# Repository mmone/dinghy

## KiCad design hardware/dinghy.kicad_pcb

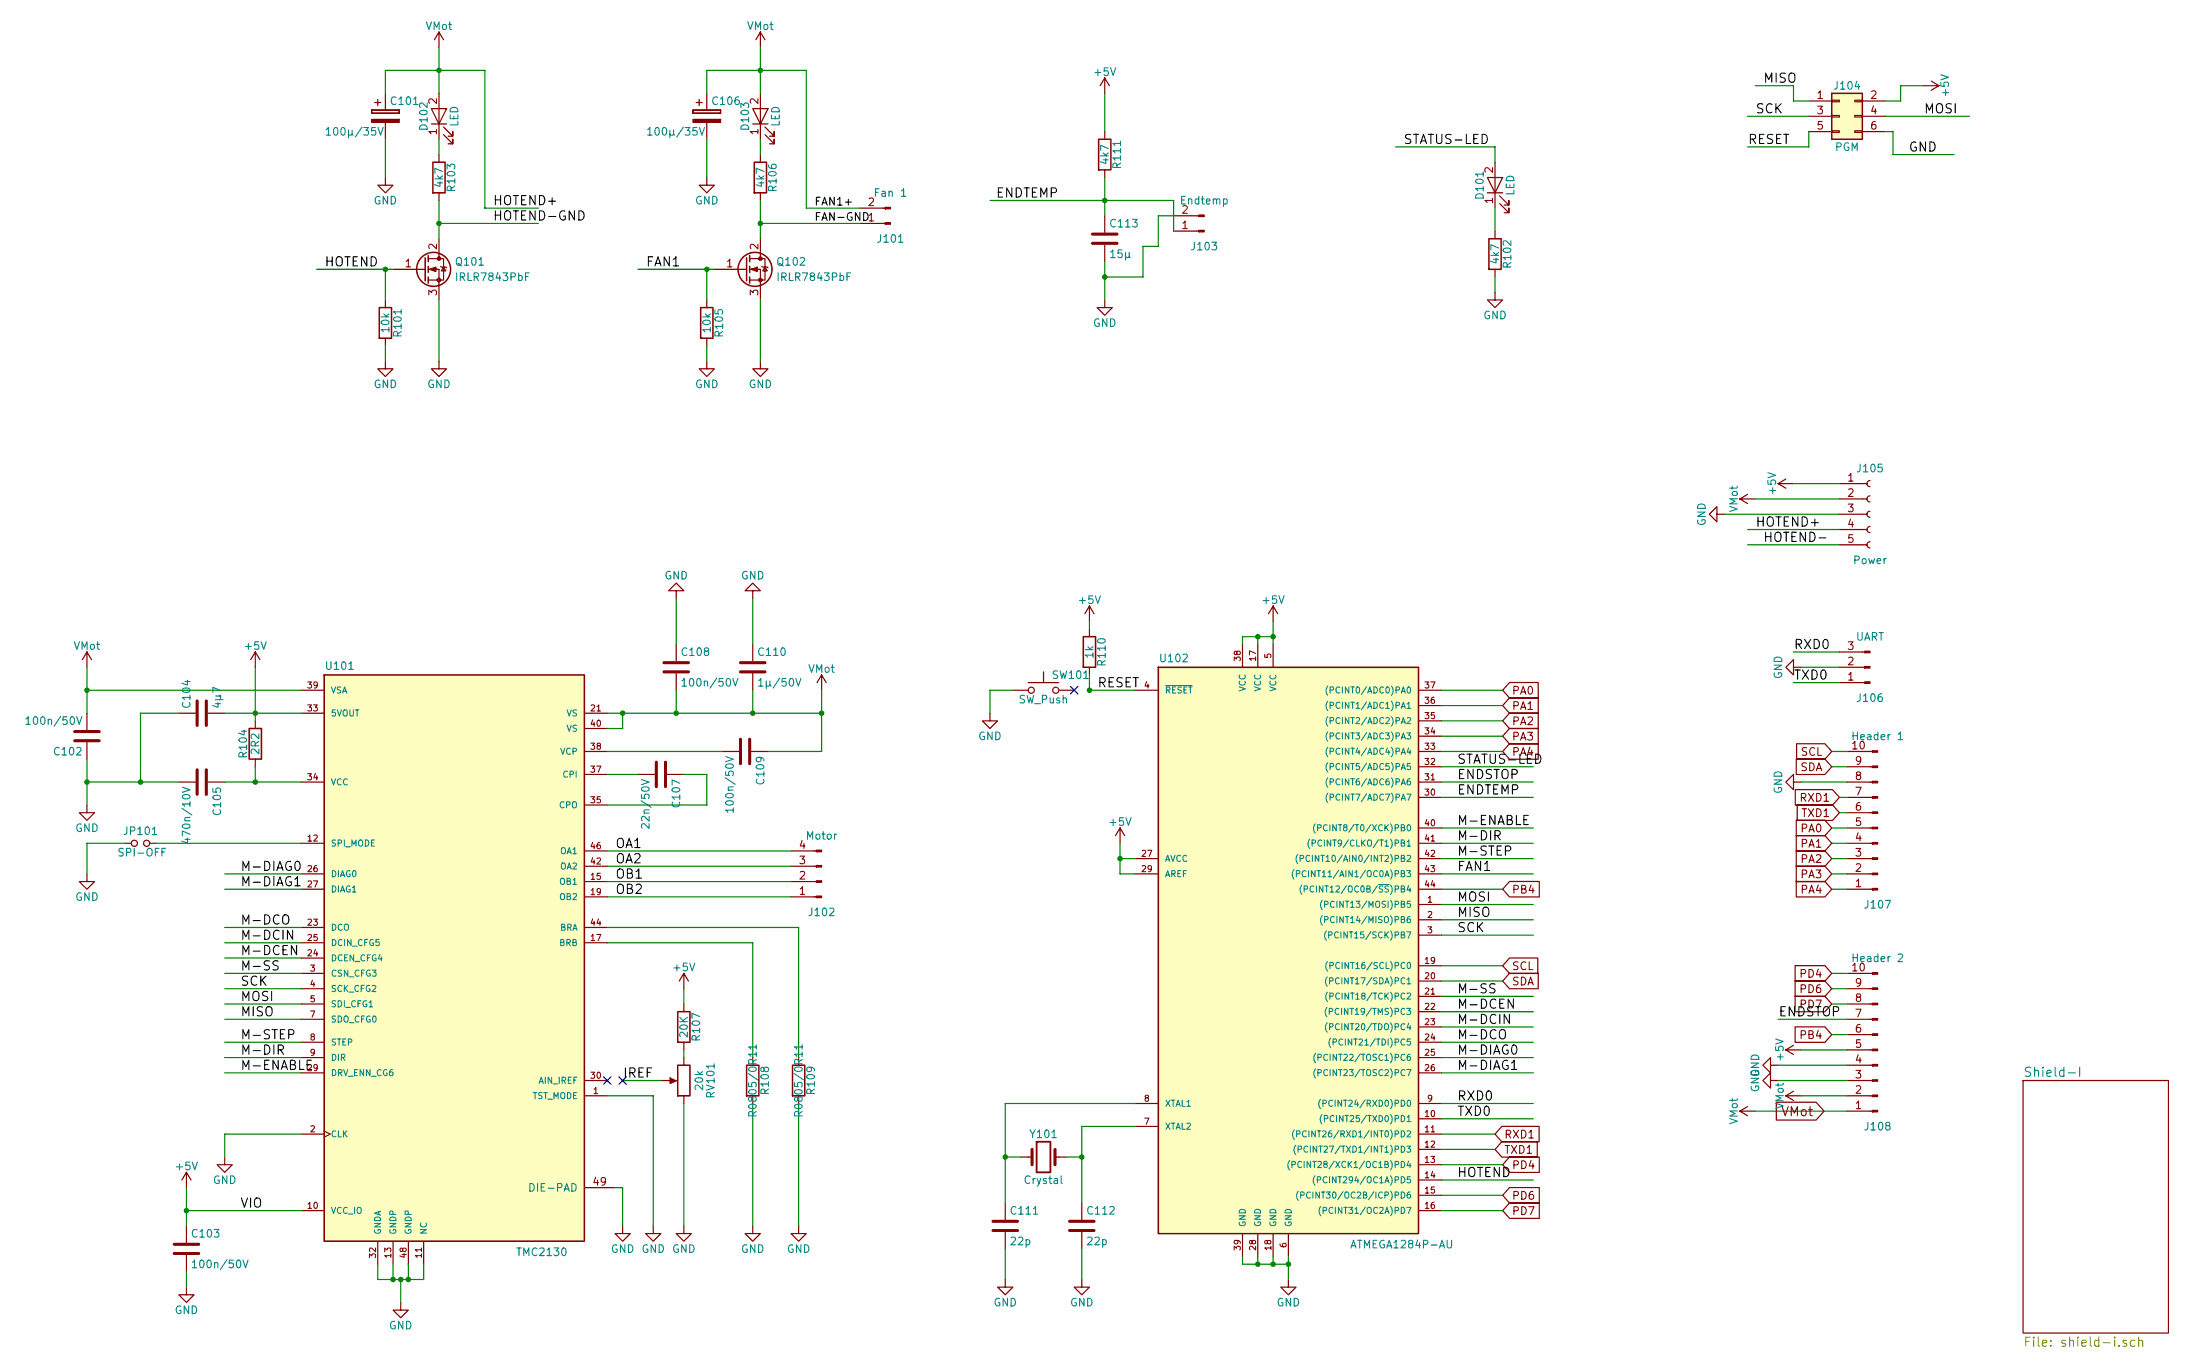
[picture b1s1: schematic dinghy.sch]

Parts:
C101, C106: 100µ/35V; CP_Elec_5x5.8
C102, C103, C108, C109: 100n/50V; C_1206_HandSoldering
C104: 4µ7; C_1206_HandSoldering
C105: 470n/10V; C_1206_HandSoldering
C107: 22n/50V; C_1206_HandSoldering
C110: 1µ/50V; C_1206_HandSoldering
C111, C112: 22p; C_1206_HandSoldering
C113: 15µ; C_1206_HandSoldering
D101, D102, D103: LED; LED_1206_HandSoldering
J101: Fan 1; JST_XH_B02B-XH-A_02x2.50mm_Straight
J102: Motor; JST_XH_B04B-XH-A_04x2.50mm_Straight
J103: Endtemp; JST_XH_B02B-XH-A_02x2.50mm_Straight
J104: PGM; Pin_Header_Straight_2x03_Pitch2.54mm
J105: Power; TerminalBlock_bornier-5_P5.08mm
J106: UART; JST_XH_B03B-XH-A_03x2.50mm_Straight
J107: Header 1; Pin_Header_Straight_1x10_Pitch2.54mm
J108: Header 2; Pin_Header_Straight_1x10_Pitch2.54mm
JP101: SPI-OFF; Pin_Header_Straight_2x01_Pitch2.54mm
Q101, Q102: IRLR7843PbF; TO-252-3_TabPin2
R101, R105: 10k; R_1206_HandSoldering
R102, R103, R106, R111: 4k7; R_1206_HandSoldering
R104: 2R2; R_1206_HandSoldering
R107: 20K; R_1206_HandSoldering
R108, R109: R0805/0R11; R_1206_HandSoldering
R110: 1k; R_1206_HandSoldering
RV101: 20k; Potentiometer_Trimmer-EVM3E
SW101: SW_Push; SW_SPST_B3S-1000
U101: TMC2130; TQFP-48-1EP_7x7mm_Pitch0.5mm
U102: ATMEGA1284P-AU; TQFP-44-1EP_10x10mm_Pitch0.8mm
Y101: Crystal; Crystal_SMD_HC49-SD

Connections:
+5V: C103.1, C104.2, J104.2, J105.1, J108.5, R104.2, R107.1, R110.1, R111.1, U101.10 (VCC_IO), U101.33 (5VOUT), U102.5 (VCC), U102.17 (VCC), U102.27 (AVCC), U102.29 (AREF), U102.38 (VCC); also elsewhere on the board
/ENDSTOP: J108.7, U102.31 ((PCINT6/ADC6)PA6)
/ENDTEMP: C113.1, J103.1, R111.2, U102.30 ((PCINT7/ADC7)PA7)
/FAN1: Q102.1 (G), R105.1, U102.43 ((PCINT11/AIN1/OC0A)PB3)
/FAN-GND: J101.1, Q102.2 (D), R106.2
/HOTEND: Q101.1 (G), R101.1, U102.14 ((PCINT294/OC1A)PD5)
/HOTEND-GND: Q101.2 (D), R103.2
/M-DCEN: U101.24 (DCEN_CFG4), U102.22 ((PCINT19/TMS)PC3)
/M-DCIN: U101.25 (DCIN_CFG5), U102.23 ((PCINT20/TDO)PC4)
/M-DCO: U101.23 (DCO), U102.24 ((PCINT21/TDI)PC5)
/M-DIAG0: U101.26 (DIAG0), U102.25 ((PCINT22/TOSC1)PC6)
/M-DIAG1: U101.27 (DIAG1), U102.26 ((PCINT23/TOSC2)PC7)
/M-DIR: U101.9 (DIR), U102.41 ((PCINT9/CLKO/T1)PB1)
/M-ENABLE: U101.29 (DRV_ENN_CG6), U102.40 ((PCINT8/T0/XCK)PB0)
/M-SS: U101.3 (CSN_CFG3), U102.21 ((PCINT18/TCK)PC2)
/M-STEP: U101.8 (STEP), U102.42 ((PCINT10/AIN0/INT2)PB2)
/MISO: J104.1, U101.7 (SDO_CFG0), U102.2 ((PCINT14/MISO)PB6)
/MOSI: J104.4, U101.5 (SDI_CFG1), U102.1 ((PCINT13/MOSI)PB5)
/OA1: J102.4, U101.46 (OA1)
/OA2: J102.3, U101.42 (OA2)
/OB1: J102.2, U101.15 (OB1)
/OB2: J102.1, U101.19 (OB2)
/RESET: J104.5, R110.2, U102.4 (~RESET)
/RXD0: J106.3, U102.9 ((PCINT24/RXD0)PD0)
/SCK: J104.3, U101.4 (SCK_CFG2), U102.3 ((PCINT15/SCK)PB7)
/STATUS-LED: D101.2 (A), U102.32 ((PCINT5/ADC5)PA5)
/TXD0: J106.1, U102.10 ((PCINT25/TXD0)PD1)
GND: C101.2, C102.1, C103.2, C104.1, C105.2, C106.2, C108.1, C110.1, C111.2, C112.2, C113.2, J103.2, J104.6, J105.3, J106.2, J107.8, J108.3, J108.4, JP101.1, Q101.3 (S), Q102.3 (S), R101.2, R102.2, R105.2, R108.2, R109.2, RV101.1, SW101.1, U101.1 (TST_MODE), U101.2 (CLK), U101.11 (NC), U101.13 (GNDP), U101.32 (GNDA), U101.48 (GNDP), U101.49 (DIE-PAD), U102.6 (GND), U102.18 (GND), U102.28 (GND), U102.39 (GND); also elsewhere on the board
unnamed: C105.1, R104.1, U101.34 (VCC)
unnamed: C107.1, U101.35 (CPO)
unnamed: C107.2, U101.37 (CPI)
unnamed: C109.2, U101.38 (VCP)
unnamed: C111.1, U102.8 (XTAL1), Y101.1
unnamed: C112.1, U102.7 (XTAL2), Y101.2
unnamed: D101.1 (K), R102.1
unnamed: D102.1 (K), R103.1
unnamed: D103.1 (K), R106.1
unnamed: JP101.2, U101.12 (SPI_MODE)
unnamed: R107.2, RV101.3
unnamed: R108.1, U101.17 (BRB)
unnamed: R109.1, U101.44 (BRA)
PA0: J107.5, U102.37 ((PCINT0/ADC0)PA0); also elsewhere on the board
PA1: J107.4, U102.36 ((PCINT1/ADC1)PA1); also elsewhere on the board
PA2: J107.3, U102.35 ((PCINT2/ADC2)PA2); also elsewhere on the board
PA3: J107.2, U102.34 ((PCINT3/ADC3)PA3); also elsewhere on the board
PA4: J107.1, U102.33 ((PCINT4/ADC4)PA4); also elsewhere on the board
PB4: J108.6, U102.44 ((PCINT12/OC0B/~SS~)PB4); also elsewhere on the board
PD4: J108.10, U102.13 ((PCINT28/XCK1/OC1B)PD4); also elsewhere on the board
PD6: J108.9, U102.15 ((PCINT30/OC2B/ICP)PD6); also elsewhere on the board
PD7: J108.8, U102.16 ((PCINT31/OC2A)PD7); also elsewhere on the board
RXD1: J107.7, U102.11 ((PCINT26/RXD1/INT0)PD2); also elsewhere on the board
SCL: J107.10, U102.19 ((PCINT16/SCL)PC0); also elsewhere on the board
SDA: J107.9, U102.20 ((PCINT17/SDA)PC1); also elsewhere on the board
TXD1: J107.6, U102.12 ((PCINT27/TXD1/INT1)PD3); also elsewhere on the board
VMot: C101.1, C102.2, C106.1, C108.2, C109.1, C110.2, D102.2 (A), D103.2 (A), J101.2, J105.2, J105.4, J108.1, J108.2, U101.21 (VS), U101.39 (VSA), U101.40 (VS); also elsewhere on the board

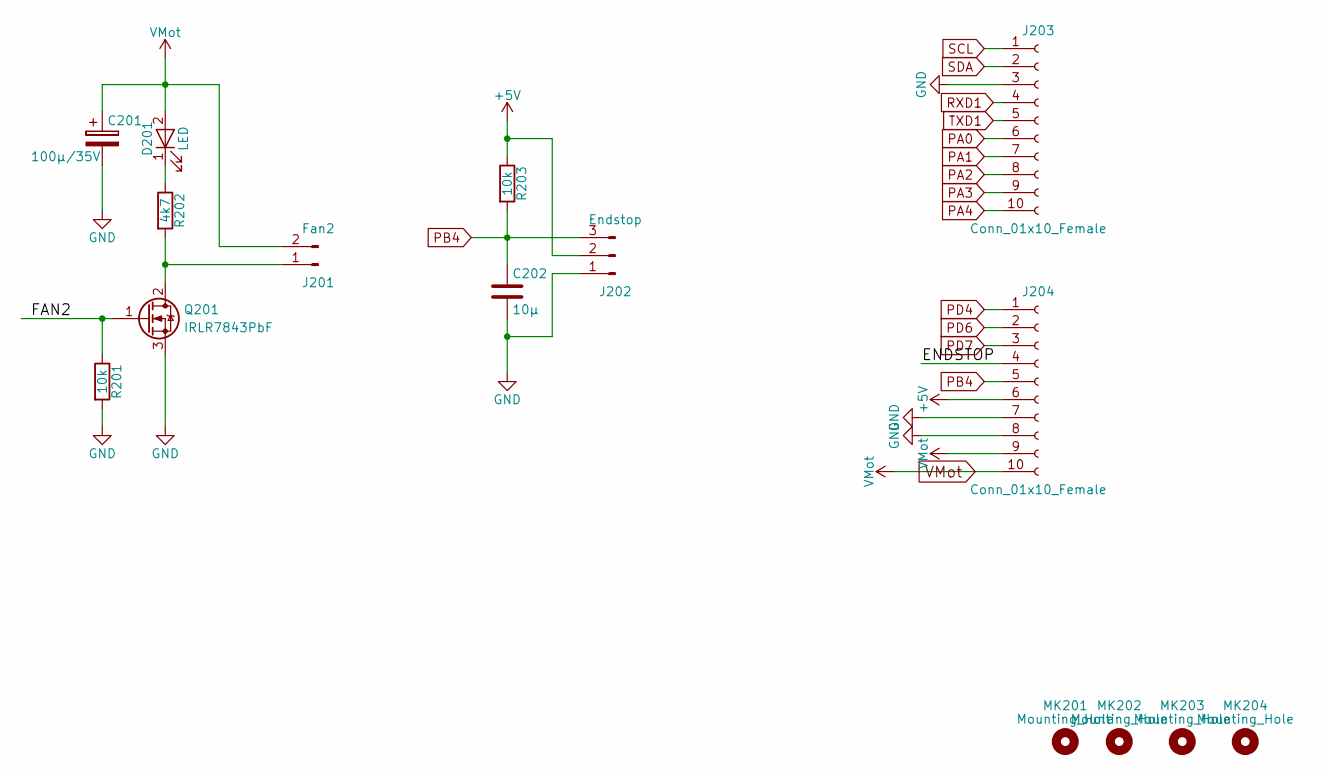
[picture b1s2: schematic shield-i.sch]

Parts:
C201: 100µ/35V; CP_Elec_5x5.8
C202: 10µ; C_1206_HandSoldering
D201: LED; LED_1206_HandSoldering
J201: Fan2; JST_XH_B02B-XH-A_02x2.50mm_Straight
J202: Endstop; JST_XH_B03B-XH-A_03x2.50mm_Straight
J203, J204: Conn_01x10_Female; Pin_Header_Straight_1x10_Pitch2.54mm
MK201, MK202, MK203, MK204: Mounting_Hole; MountingHole_3mm
Q201: IRLR7843PbF; TO-252-3_TabPin2
R201, R203: 10k; R_1206_HandSoldering
R202: 4k7; R_1206_HandSoldering

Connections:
+5V: J202.2, J204.6, R203.1; also elsewhere on the board
/Shield-I/FAN2: Q201.1 (G), R201.1
GND: C201.2, C202.2, J202.1, J203.3, J204.7, J204.8, Q201.3 (S), R201.2; also elsewhere on the board
unnamed: D201.1 (K), R202.1
unnamed: J201.1, Q201.2 (D), R202.2
PA0: J203.6; also elsewhere on the board
PA1: J203.7; also elsewhere on the board
PA2: J203.8; also elsewhere on the board
PA3: J203.9; also elsewhere on the board
PA4: J203.10; also elsewhere on the board
PB4: C202.1, J202.3, J204.5, R203.2; also elsewhere on the board
PD4: J204.1; also elsewhere on the board
PD6: J204.2; also elsewhere on the board
PD7: J204.3; also elsewhere on the board
RXD1: J203.4; also elsewhere on the board
SCL: J203.1; also elsewhere on the board
SDA: J203.2; also elsewhere on the board
TXD1: J203.5; also elsewhere on the board
VMot: C201.1, D201.2 (A), J201.2, J204.9, J204.10; also elsewhere on the board

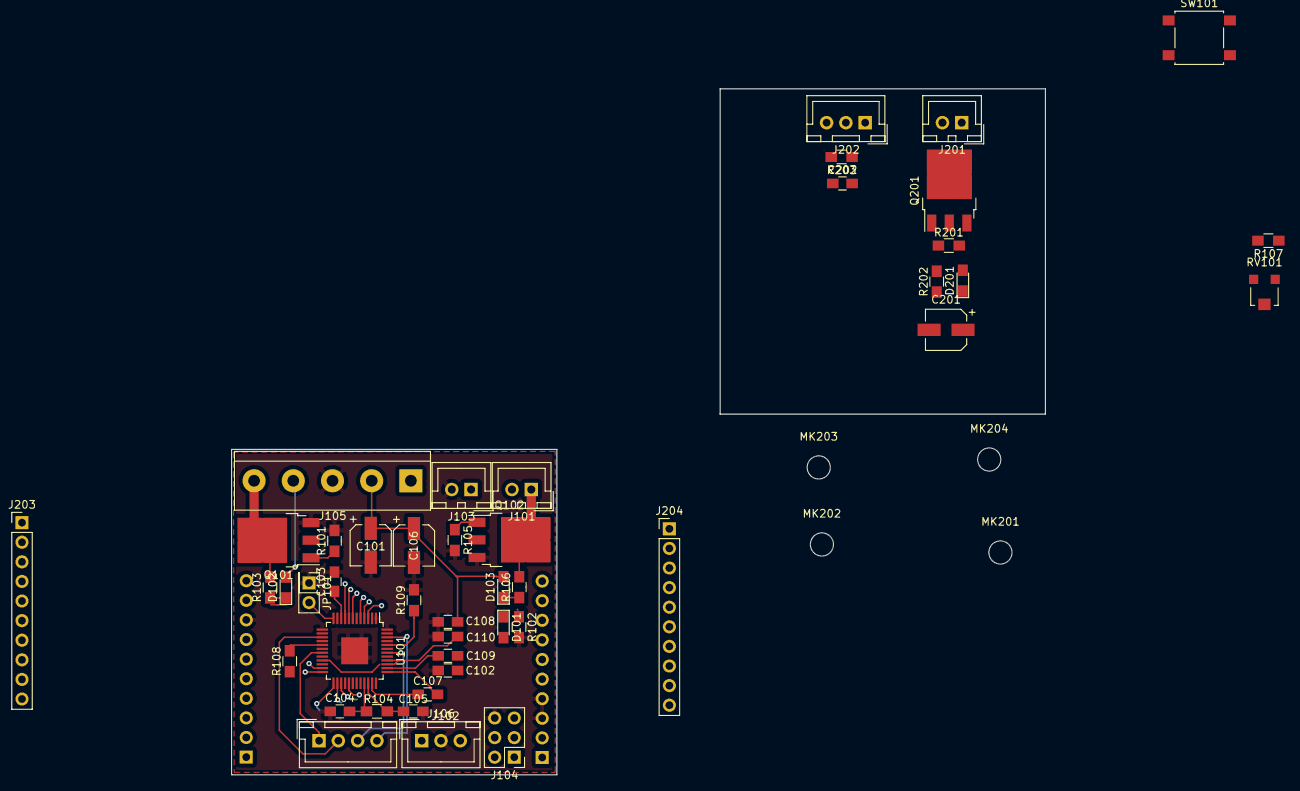
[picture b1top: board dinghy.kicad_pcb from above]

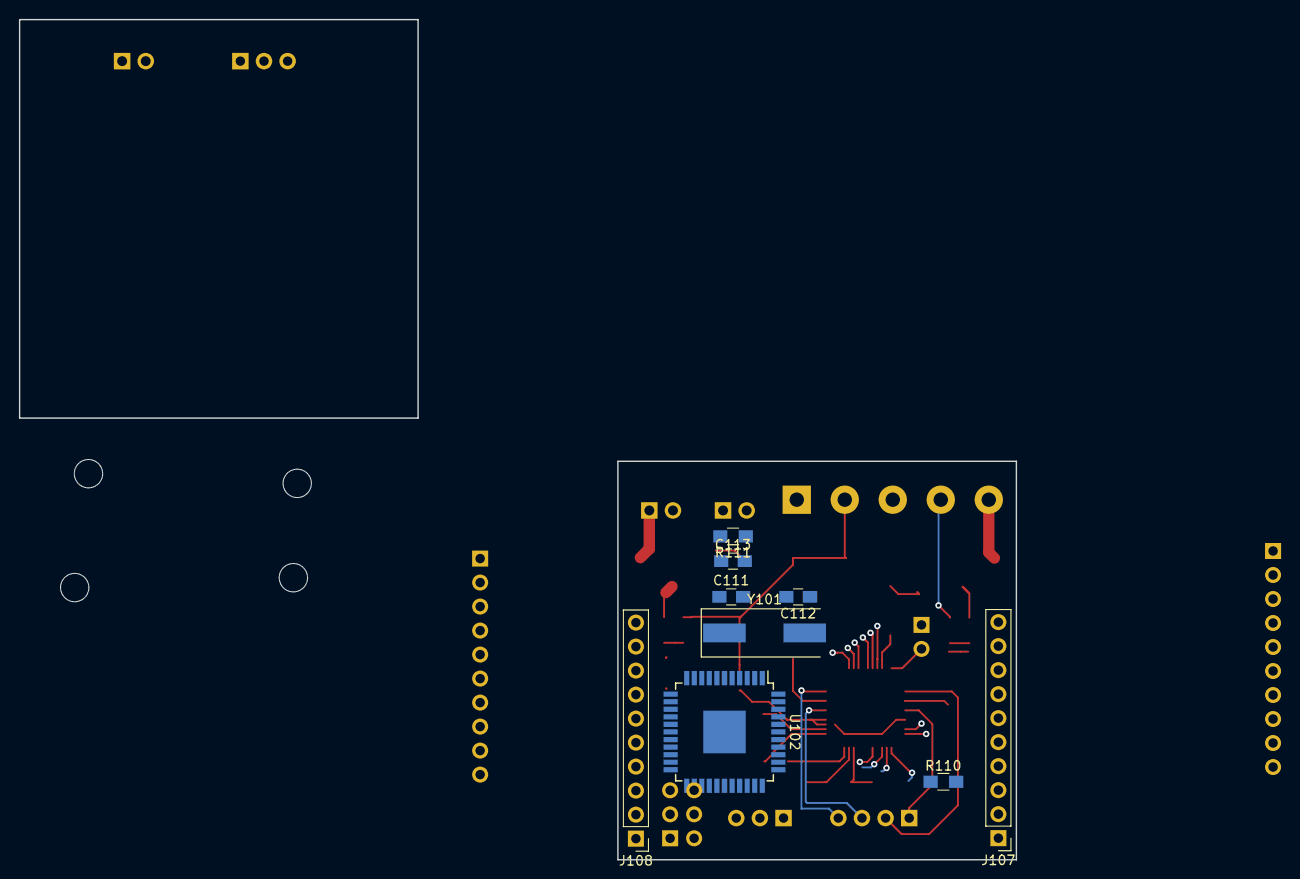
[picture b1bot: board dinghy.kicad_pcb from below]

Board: 2 copper layers, 105.5 x 88.9 mm, 58 parts (9 on the bottom side), 58 nets.

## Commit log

2018-02-12 Renamed power net
2018-02-13 Basic layout done.
2018-02-13 Split second board of to seperate schematic
2018-02-14 Components positioned
2018-02-14 Moved custom trinamic lib into project dir
2018-02-15 Top layer routet
